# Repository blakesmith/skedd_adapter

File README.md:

# skedd_adapter

A SKEDD JTAG / SWD Adapter Board. Used to adapt a standard 1.27mm pitch JTAG connector to a [Würth Elektronik SKEDD cable connector](https://www.digikey.com/en/products/detail/w%C3%BCrth-elektronik/490107670412S/10315621)

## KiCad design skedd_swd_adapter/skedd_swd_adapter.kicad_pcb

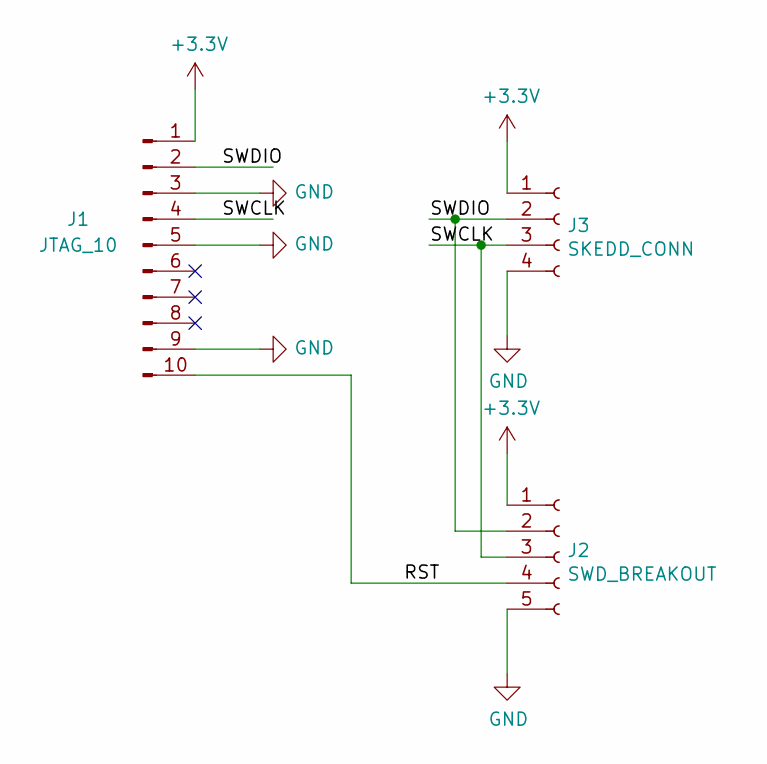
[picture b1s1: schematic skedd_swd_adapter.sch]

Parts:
J1: JTAG_10; Pin_Header_Straight_2x05_Pitch1.27mm_SMD
J2: SWD_BREAKOUT; Pin_Header_Straight_1x05_Pitch2.54mm
J3: SKEDD_CONN; REDFIT_IDC_SKEDD_CONN_4PIN

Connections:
+3V3: J1.1, J2.1, J3.1
/RST: J1.10, J2.4
/SWCLK: J1.4, J2.3, J3.3
/SWDIO: J1.2, J2.2, J3.2
GND: J1.3, J1.5, J1.9, J2.5, J3.4

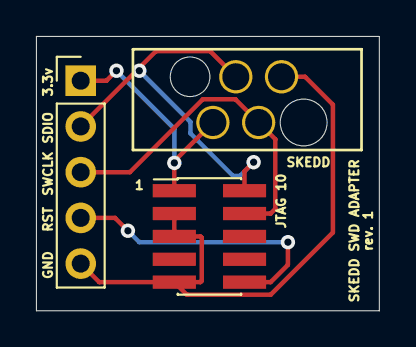
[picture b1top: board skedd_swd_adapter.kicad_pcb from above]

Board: 2 copper layers, 19.1 x 15.2 mm, 3 parts (0 on the bottom side), 5 nets.

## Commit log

2020-12-03 Add skedd swd adapter
